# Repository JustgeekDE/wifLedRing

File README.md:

# WiFi LED ring
An LED ring inspired by Adafruits neopixel rings. With an ESP8266 WiFi module. Since the WiFi module and the LEDs are powered both from the same source, thi input voltage is limited to the 3.3-3.7V range. A small LiPo or Li-Ion battery is recommended

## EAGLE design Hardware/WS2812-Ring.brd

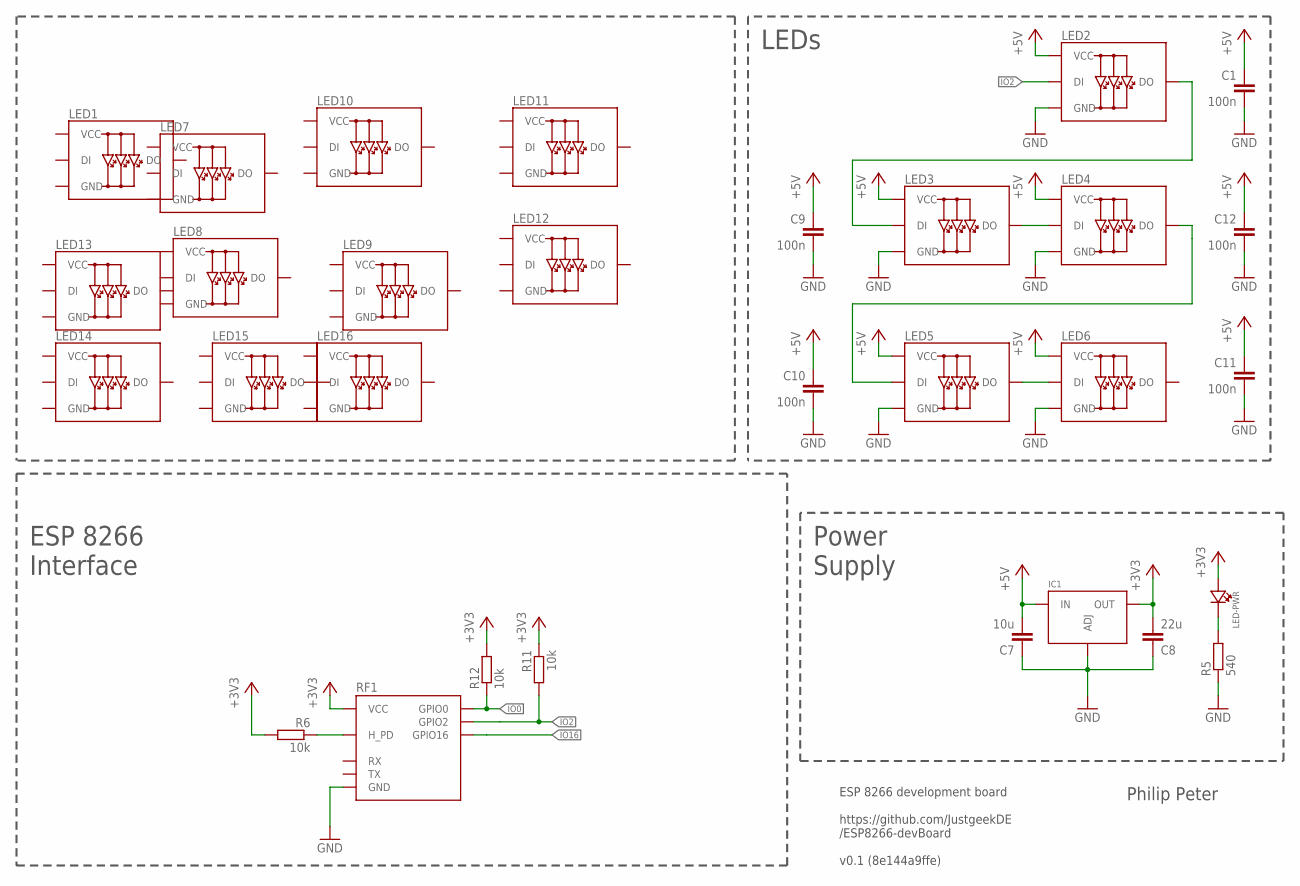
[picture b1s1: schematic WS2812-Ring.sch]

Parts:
C1, C9, C10, C11, C12: 100n; C0805
C7: 10u; C0805
C8: 22u; C0805
IC1: REGULATOR-LM317-SOT223; SOT223
LED1, LED2, LED3, LED4, LED5, LED6, LED7, LED8, LED9, LED10, LED11, LED12, LED13, LED14, LED15, LED16: WS2812B; CHIP-5050-4_PIN
LED-PWR: LED0805; CHIPLED_0805
R5: 540; R0805
R6, R11, R12: 10k; R0805
RF1: ESP2866-ESP-01THT; ESP8266-ESP-01

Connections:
+3V3: C8.2, IC1.2 (OUT), IC1.4 (OUT), LED-PWR.A, R6.2, R11.1, R12.2, RF1.VCC
+5V: C1.1, C7.2, C9.1, C10.1, C11.1, C12.1, IC1.3 (IN), LED2.P$1 (VCC), LED3.P$1 (VCC), LED4.P$1 (VCC), LED5.P$1 (VCC), LED6.P$1 (VCC)
GND: C1.2, C7.1, C8.1, C9.2, C10.2, C11.2, C12.2, IC1.1 (ADJ), LED2.P$3 (GND), LED3.P$3 (GND), LED4.P$3 (GND), LED5.P$3 (GND), LED6.P$3 (GND), R5.1, RF1.GND
IO0: R12.1, RF1.GPIO0
IO2: LED2.P$4 (DI), R11.2, RF1.GPIO2
IO16: RF1.GPIO16
unnamed: LED-PWR.C, R5.2
unnamed: LED2.P$2 (DO), LED3.P$4 (DI)
unnamed: LED3.P$2 (DO), LED4.P$4 (DI)
unnamed: LED4.P$2 (DO), LED5.P$4 (DI)
unnamed: LED5.P$2 (DO), LED6.P$4 (DI)
RESET: R6.1, RF1.H_PD

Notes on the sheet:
ESP 8266 Interface
Power Supply
Philip Peter
ESP 8266 development board https://github.com/JustgeekDE /ESP8266-devBoard v0.1 (8e144a9ffe)
LEDs

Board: 2 copper layers, 31 parts (13 on the bottom side), 11 nets, no tracks yet.

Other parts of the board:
U$3: LOGO-JUSTGEEK-XS

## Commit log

2015-05-30 Initial checkin
2015-05-31 Added readme
